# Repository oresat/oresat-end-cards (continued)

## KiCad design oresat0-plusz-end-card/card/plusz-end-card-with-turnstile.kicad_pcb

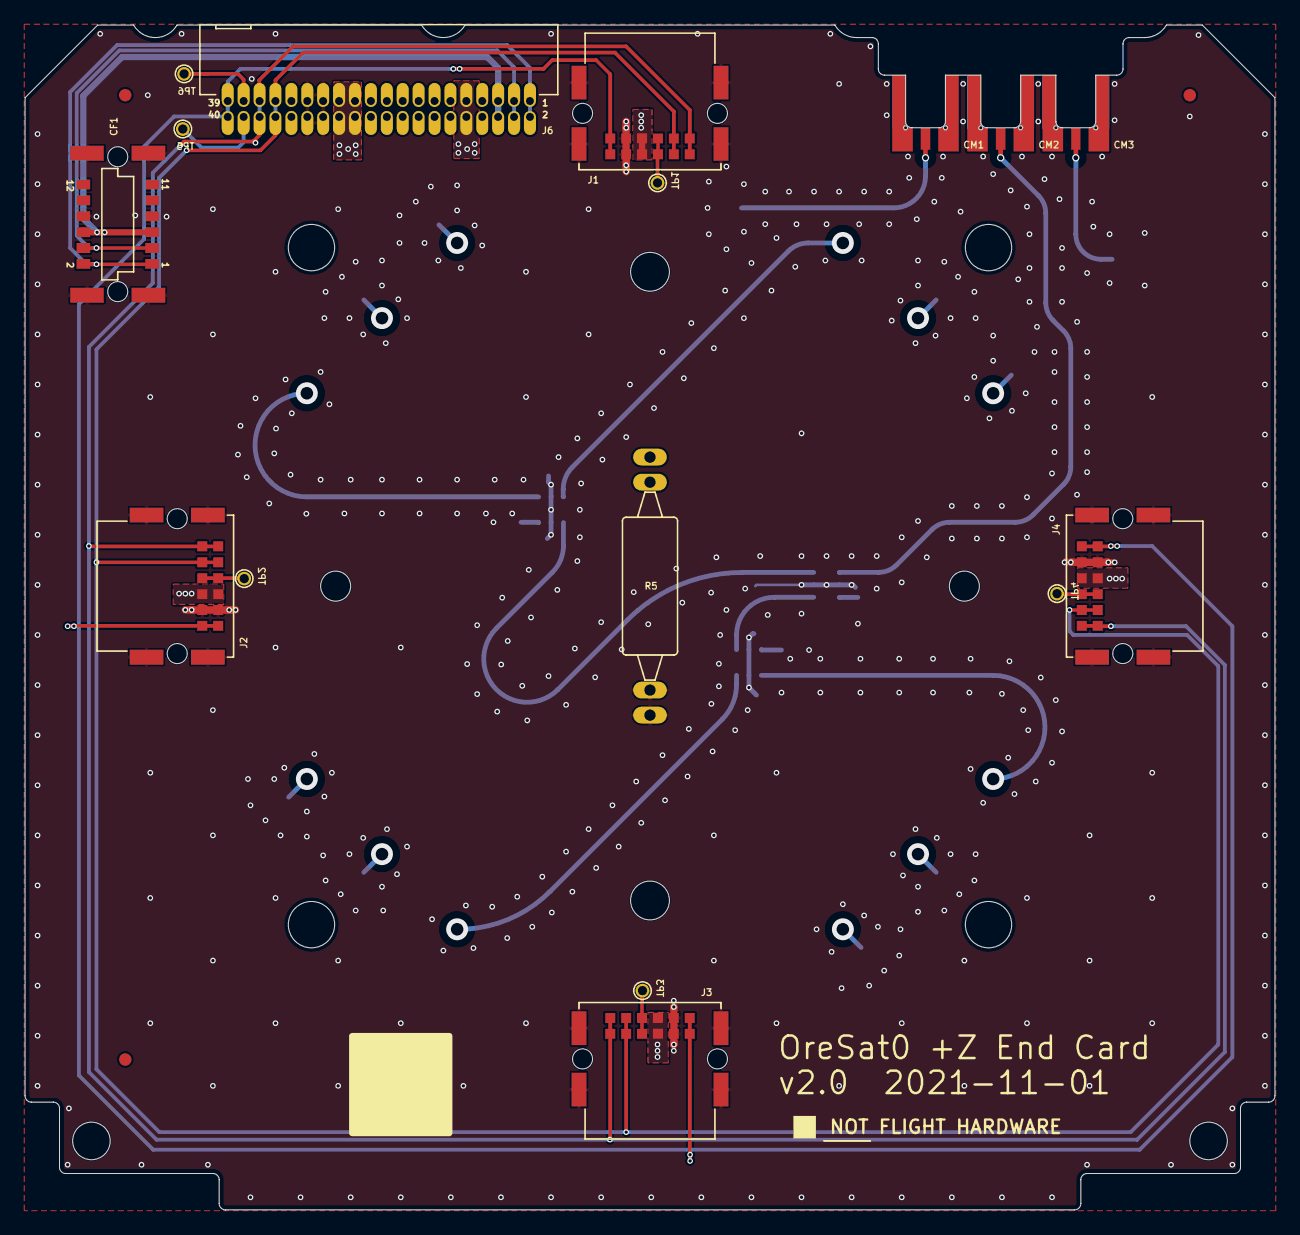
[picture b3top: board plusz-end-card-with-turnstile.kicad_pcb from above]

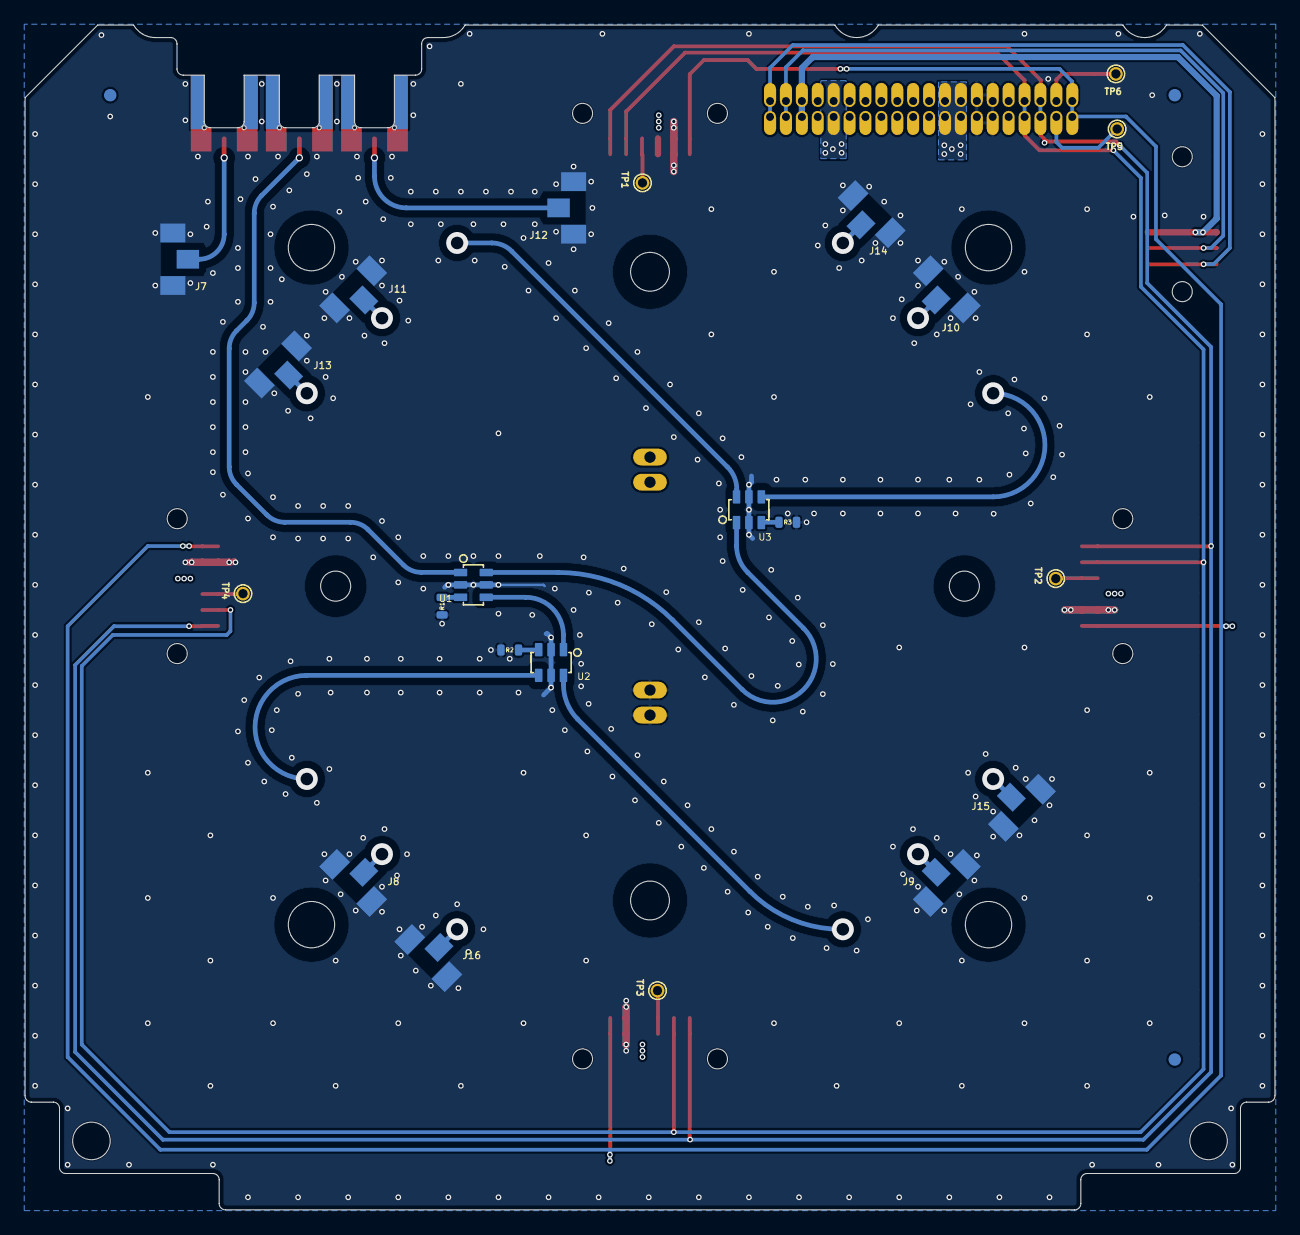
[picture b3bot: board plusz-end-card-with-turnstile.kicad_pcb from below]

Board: 4 copper layers, 99.8 x 94.6 mm, 48 parts (19 on the bottom side), 23 nets.

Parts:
CF1: J-HARWIN-M55-6001242R; HARWIN-M55-60X1242R
CM1, CM2, CM3: J-MOLEX-SMPM-73300-003X; J-MOLEX-SMPM-073300-003X
FIDUCIAL1, FIDUCIAL2, FIDUCIAL3, FIDUCIAL4, FIDUCIAL5, FIDUCIAL6: FIDUCIAL-1.0X2.0
HW1, HW2, HW3, HW4: MCMASTER-94100A150
J1, J2, J3, J4: Harwin M55-7101242R; M55-7101242R
J6: J-SAMTEC-TFM-120-X1-XXX-D-RA
J7, J8, J9, J10, J11, J12, J13, J14, J15, J16: R107064070_CONTACT
PCB1: ORESAT-CARD-V1.3-GENERIC-3RF
R1, R2, R3: 50; .0603-C-NOSILK
R5: 7.5 1W; PAC100-FOR-MELTWIRE
TP1, TP2, TP3, TP4, TP5, TP6: TEST-POINT-LARGE-SQUARE; 1X01
U1, U2, U3: QCN-19+; QCN-XXX+
U$1: FLIGHMARKERNEW; FLIGHTMARKER_NEW_BOARDS
UNK_HOLE_0: dummyfp0
UNK_HOLE_1: dummyfp1
UNK_HOLE_2: dummyfp2
UNK_HOLE_3: dummyfp3

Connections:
/CONNECTORS/C3-UART-RX: J6.38, TP5.1 (1_1)
/CONNECTORS/C3-UART-TX: J6.37, TP6.1 (1_1)
/CONNECTORS/CAN1_H: J1.9 (CANH), J1.10 (CANH), J2.9 (CANH), J2.10 (CANH), J3.9 (CANH), J3.10 (CANH), J4.9 (CANH), J4.10 (CANH), J6.33, J6.34
/CONNECTORS/CAN1_L: J1.11 (CANL), J1.12 (CANL), J2.11 (CANL), J2.12 (CANL), J3.11 (CANL), J3.12 (CANL), J4.11 (CANL), J4.12 (CANL), J6.35, J6.36
/CONNECTORS/MAG-POWER: CF1.5, CF1.6, J6.5, J6.6
/CONNECTORS/MAG-SCL: CF1.3, CF1.4, J6.3, J6.4
/CONNECTORS/MAG-SDA: CF1.1, CF1.2, J6.1, J6.2
/CONNECTORS/TURNSTILE-DEPLOY: J6.9, J6.10, R5.P$3 (2), R5.P$4 (2)
/CONNECTORS/VBUS: J1.5 (VBUS), J1.6 (VBUS), J2.5 (VBUS), J2.6 (VBUS), J3.5 (VBUS), J3.6 (VBUS), J4.5 (VBUS), J4.6 (VBUS), J6.23, J6.24, J6.25, J6.26
/CONNECTORS/~SD: J1.1 (~SD), J1.2 (~SD), J2.1 (~SD), J2.2 (~SD), J3.1 (~SD), J3.2 (~SD), J4.1 (~SD), J4.2 (~SD), J6.39, J6.40
/L1 BAND/RF-L1BAND: CM1.RF (CENTER), J12.P$1
/L BAND/RF-LBAND: CM2.RF (CENTER), U1.1 (SUM)
/L BAND/RF-LBAND-1/4L: U1.6 (PORT2), U3.1 (SUM)
/L BAND/RF-LBAND-SHORT: U1.4 (PORT1), U2.1 (SUM)
/UHF/RF-UHF: CM3.RF (CENTER), J7.P$1
GND: CF1.7, CF1.8, CF1.P$1 (SHIELDS), CF1.P$2 (SHIELDS), CF1.P$3 (SHIELDS), CF1.P$4 (SHIELDS), CM1.P$1 (SHIELD3), CM1.P$2 (SHIELD2), CM1.P$3 (SHIELD1), CM1.P$4 (SHIELD), CM2.P$1 (SHIELD3), CM2.P$2 (SHIELD2), CM2.P$3 (SHIELD1), CM2.P$4 (SHIELD), CM3.P$1 (SHIELD3), CM3.P$2 (SHIELD2), CM3.P$3 (SHIELD1), CM3.P$4 (SHIELD), J1.3 (GND), J1.4 (GND), J1.P$1 (SHIELD), J1.P$2 (SHIELD), J1.P$3 (SHIELD), J1.P$4 (SHIELD), J2.3 (GND), J2.4 (GND), J2.P$1 (SHIELD), J2.P$2 (SHIELD), J2.P$3 (SHIELD), J2.P$4 (SHIELD), J3.3 (GND), J3.4 (GND), J3.P$1 (SHIELD), J3.P$2 (SHIELD), J3.P$3 (SHIELD), J3.P$4 (SHIELD), J4.3 (GND), J4.4 (GND), J4.P$1 (SHIELD), J4.P$2 (SHIELD), J4.P$3 (SHIELD), J4.P$4 (SHIELD), J6.27, J6.28, J6.29, J6.30, J7.P$2, J7.P$3, J8.P$2, J8.P$3, J9.P$2, J9.P$3, J10.P$2, J10.P$3, J11.P$2, J11.P$3, J12.P$2, J12.P$3, J13.P$2, J13.P$3, J14.P$2, J14.P$3, J15.P$2, J15.P$3, J16.P$2, J16.P$3, R1.1, R2.1, R3.1, R5.P$1 (1), R5.P$2 (1), U1.2 (GND), U1.5 (GND), U2.2 (GND), U2.5 (GND), U3.2 (GND), U3.5 (GND)
unnamed: J1.7 (AUX), J1.8 (AUX), TP1.1 (1_1)
unnamed: J2.7 (AUX), J2.8 (AUX), TP2.1 (1_1)
unnamed: J3.7 (AUX), J3.8 (AUX), TP3.1 (1_1)
unnamed: J4.7 (AUX), J4.8 (AUX), TP4.1 (1_1)
unnamed: R1.2, U1.3 (TERM)
unnamed: R2.2, U2.3 (TERM)
unnamed: R3.2, U3.3 (TERM)

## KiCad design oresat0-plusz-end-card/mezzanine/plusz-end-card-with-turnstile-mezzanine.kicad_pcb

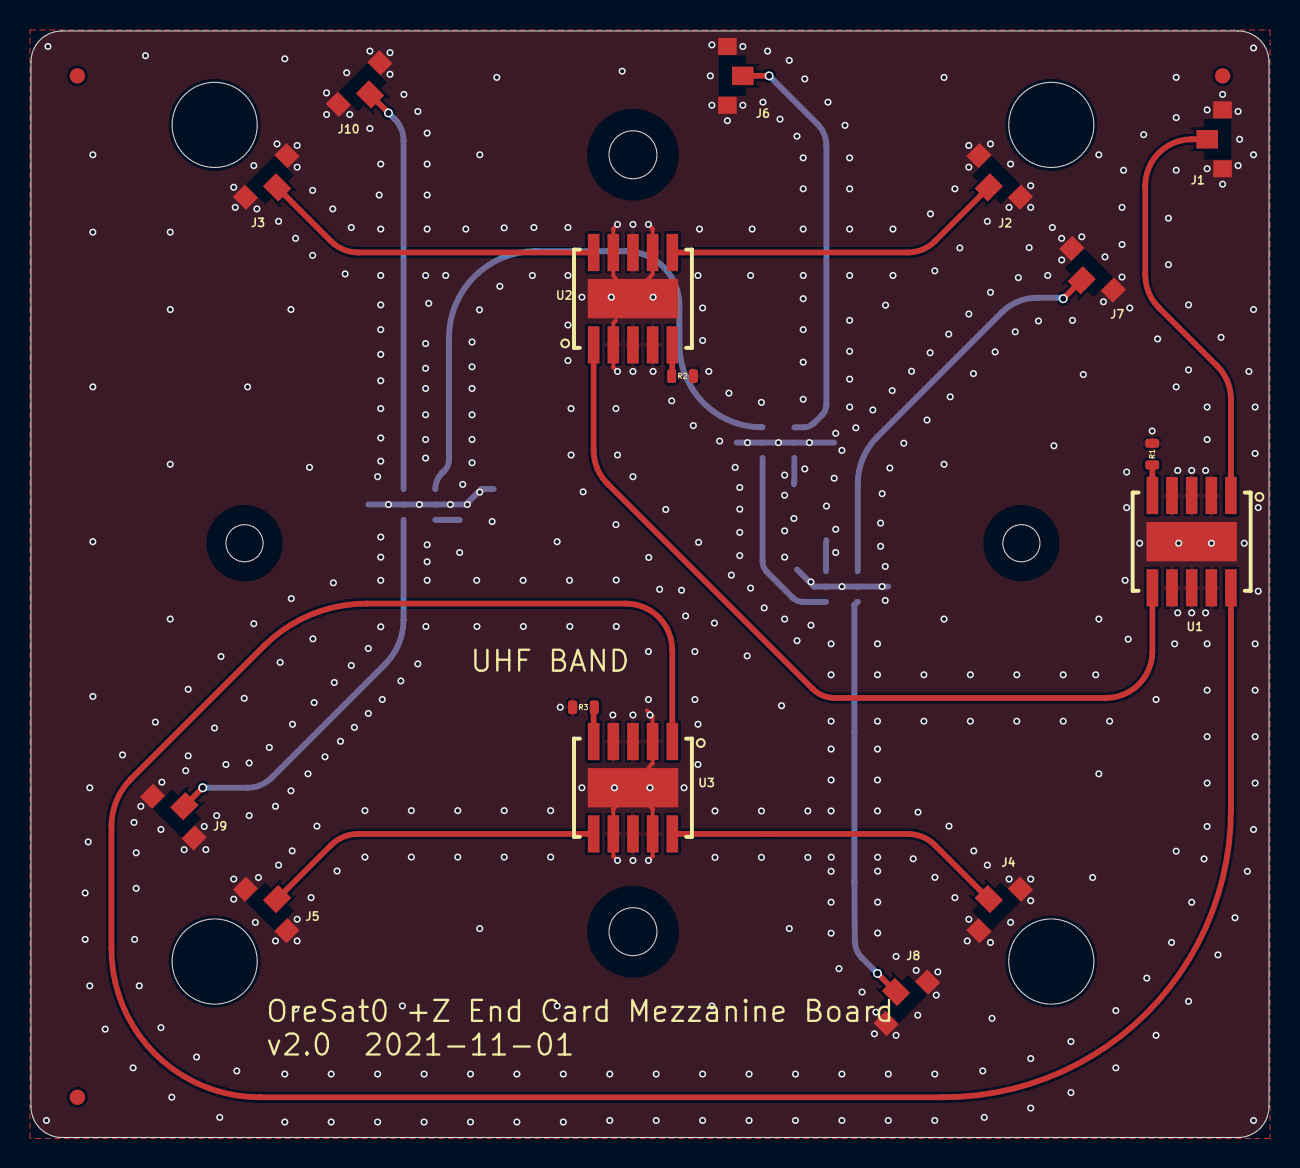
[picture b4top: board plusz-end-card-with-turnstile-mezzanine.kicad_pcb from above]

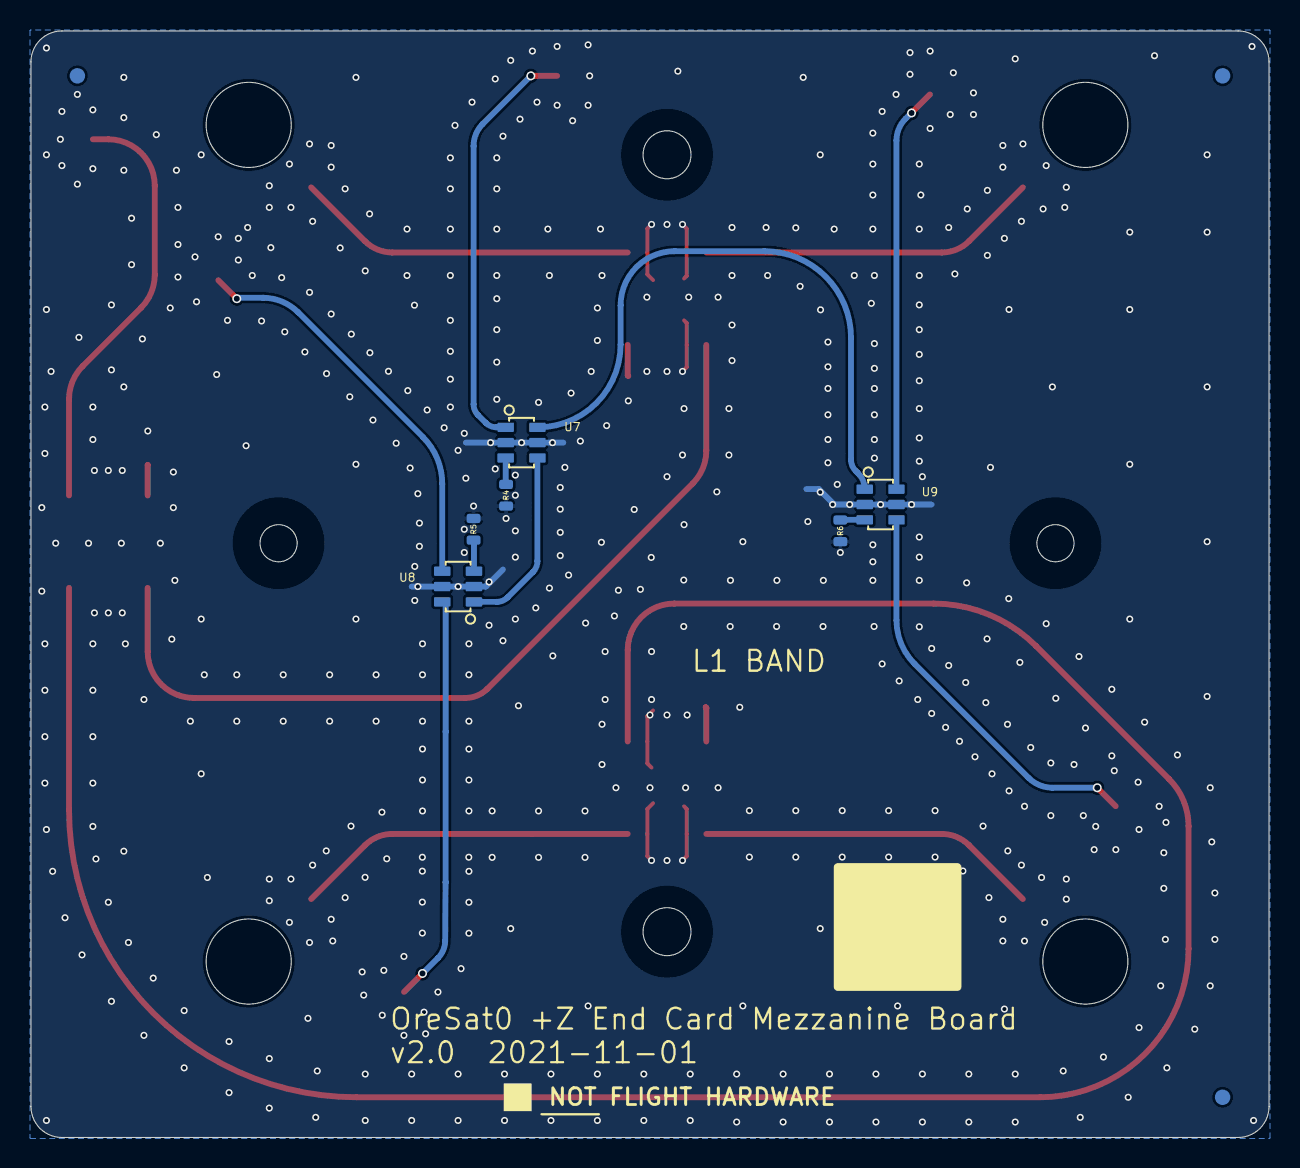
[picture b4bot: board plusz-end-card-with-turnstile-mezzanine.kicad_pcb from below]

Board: 4 copper layers, 80.0 x 71.5 mm, 37 parts (10 on the bottom side), 21 nets.

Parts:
FIDUCIAL1, FIDUCIAL2, FIDUCIAL3, FIDUCIAL4, FIDUCIAL6, FIDUCIAL7: FIDUCIAL-1.0X2.0
J1, J2, J3, J4, J5, J6, J7, J8, J9, J10: R107064070; R107064070_SOLDER
R1, R2, R3, R4, R5, R6: 50; .0603-C-NOSILK
U1, U2, U3: QBA-07+
U7, U8, U9: QCN-19+; QCN-XXX+
U$1: FLIGHMARKERNEW; FLIGHTMARKER_NEW_BOARDS
UNK_HOLE_0: dummyfp0
UNK_HOLE_1: dummyfp1
UNK_HOLE_2: dummyfp2
UNK_HOLE_3: dummyfp3
UNK_HOLE_4: dummyfp4
UNK_HOLE_5: dummyfp5
UNK_HOLE_6: dummyfp6
UNK_HOLE_7: dummyfp7

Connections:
GND: J1.P$2, J1.P$3, J2.P$2, J2.P$3, J3.P$2, J3.P$3, J4.P$2, J4.P$3, J5.P$2, J5.P$3, J6.P$2, J6.P$3, J7.P$2, J7.P$3, J8.P$2, J8.P$3, J9.P$2, J9.P$3, J10.P$2, J10.P$3, R1.1, R2.1, R3.1, R4.1, R5.1, R6.1, U1.2, U1.3, U1.4, U1.7, U1.8, U1.9, U1.GND-NO-PAD, U2.2, U2.3, U2.4, U2.7, U2.8, U2.9, U2.GND-NO-PAD, U3.2, U3.3, U3.4, U3.7, U3.8, U3.9, U3.GND-NO-PAD, U7.2, U7.5, U8.2, U8.5, U9.2, U9.5
L1BAND: J6.P$1, U7.1
L1BAND-SHORT: U7.4, U8.1
L1BAND-SHORT+1/4WAVE: U7.6, U9.1
L1BAND_0: J7.P$1, U8.4
L1BAND_90: J8.P$1, U8.6
L1BAND_180: J9.P$1, U9.4
L1BAND_270: J10.P$1, U9.6
unnamed: R4.2, U7.3
unnamed: R5.2, U8.3
unnamed: R1.2, U1.5
unnamed: R2.2, U2.5
unnamed: R6.2, U9.3
unnamed: R3.2, U3.5
UHF: J1.P$1, U1.1
UHF-SHORT: U1.6, U2.1
UHF-SHORT+1/4WAVE: U1.10, U3.1
UHF_0: J2.P$1, U2.6
UHF_90: J3.P$1, U2.10
UHF_180: J5.P$1, U3.6
UHF_270: J4.P$1, U3.10

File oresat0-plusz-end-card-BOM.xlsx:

Bill Of Materials for OreSat0 +Z End Card and Mezzanine
Last modified: 2021/11/01
PCB version: 2.0 |  |  | P/DNP = | Place/Do Not Place (DNP is for final production boards)
BOM revision: 0 |  |  | Generic = | Any generic part with the same characteristics are OK (e.g., bypass cap)
 | +Z END CARD
Cnt | Part References | P/DNP | Mfg | Mfg PN | Description | Generic | Dist | Dist Part Number | Stock | Cost | Cost Ext.
1 | CF1 | P | Harwin Inc. | M55-6001242R | 12 Position Receptacle Connector 0.050" (1.27mm) Surface Mount Gold | N | Digi-Key | 952-3835-1-ND | 7 | 1.74 | 1.74
3 | CM1, CM2, CM3 | P | Molex | 73300-0020 | SMPM Connector Plug, Male Pin 50Ohm Board Edge | N | Digi-Key | WM10772-ND | 0 | 16.41 | 49.230000000000004
4 | HW1, HW2, HW3, HW4 | P | McMaster Carr | 94100A150 | M2 x 0.4 mm 18-8 Stainless Steel Press-Fit Nut | N | McMaster Carr | 94100A150 | 24 | 0.56200000000000006 | 2.2480000000000002
4 | J1, J2, J3, J4 | P | Harwin Inc. | M55-7101242R | CONN HEADER SMD R/A 12POS 1.27MM -- Solar connectors | N | Digi-Key | 952-3891-1-ND | 30 | 1.46 | 5.8399999999999999
1 | J6 | P | Samtec Inc. | TFM-120-01-L-D-RA | CONN HEADER R/A 40POS 1.27MM - Main OreSat connector | N | Digi-Key | SAM10145-ND | 19 | 10.119999999999999 | 10.119999999999999
3 | R1, R2, R3 | P | Vishay Dale | RCP0603W50R0GEB | RES SMD 50 OHM 2% 1.5W 0603 | N | Digi-Key | 541-2655-1-ND | 20 | 1.8400000000000001 | 5.5200000000000005
1 | R4 | P | Vishay | PAC100007508FA1000 | Res 7.5 ohm 1W 1% Axial high temperature | N | Digi-Key | PPC1D1.0CT-ND | 4 | 0.77000000000000002 | 0.77000000000000002
3 | U1, U2, U3 | P | Mini-Circuits | QCN-19+ | Power Splitter/Combiner, 2 Way-90°, 50Ω, 1100-1925 Mhz, LTCC | N | Mouser | 139-QCN-19 | 7 | 13.949999999999999 | 41.849999999999994
 | MEZZANINE
Cnt | Part References | P/DNP | Mfg | Mfg PN | Description | Generic | Dist | Dist Part Number |  | Cost | Cost Ext.
10 | J1, J2, J3, J4, J5, J6, J7, J8, J9, J10 | P | Radiall | R107064070 | Spring RF connectors | N | Mouser | 501-R107064070 | 29 | 5.1500000000000004 | 51.5
6 | R1, R2, R3, R4, R5, R6 | P | Vishay Dale | RCP0603W50R0GEB | RES SMD 50 OHM 2% 1.5W 0603 | N | Digi-Key | 541-2655-1-ND | 20 | 1.8400000000000001 | 11.040000000000001
3 | U1, U2, U3 | P | Mini-Circuits | QBA-07+ | Power Splitter/Combiner, 2 Way-90°, 50Ω, 340-680 Mhz, LTCC | N | Mini-Circuits | QBA-07+ | 8 | 6.9500000000000002 | 20.850000000000001
3 | U7, U8, U9 | P | Mini-Circuits | QCN-19+ | Power Splitter/Combiner, 2 Way-90°, 50Ω, 1100-1925 Mhz, LTCC | N | Mouser | 139-QCN-19 | 7 | 13.949999999999999 | 41.849999999999994
 |  |  |  |  |  |  |  | Total |  |  | 242.55799999999999

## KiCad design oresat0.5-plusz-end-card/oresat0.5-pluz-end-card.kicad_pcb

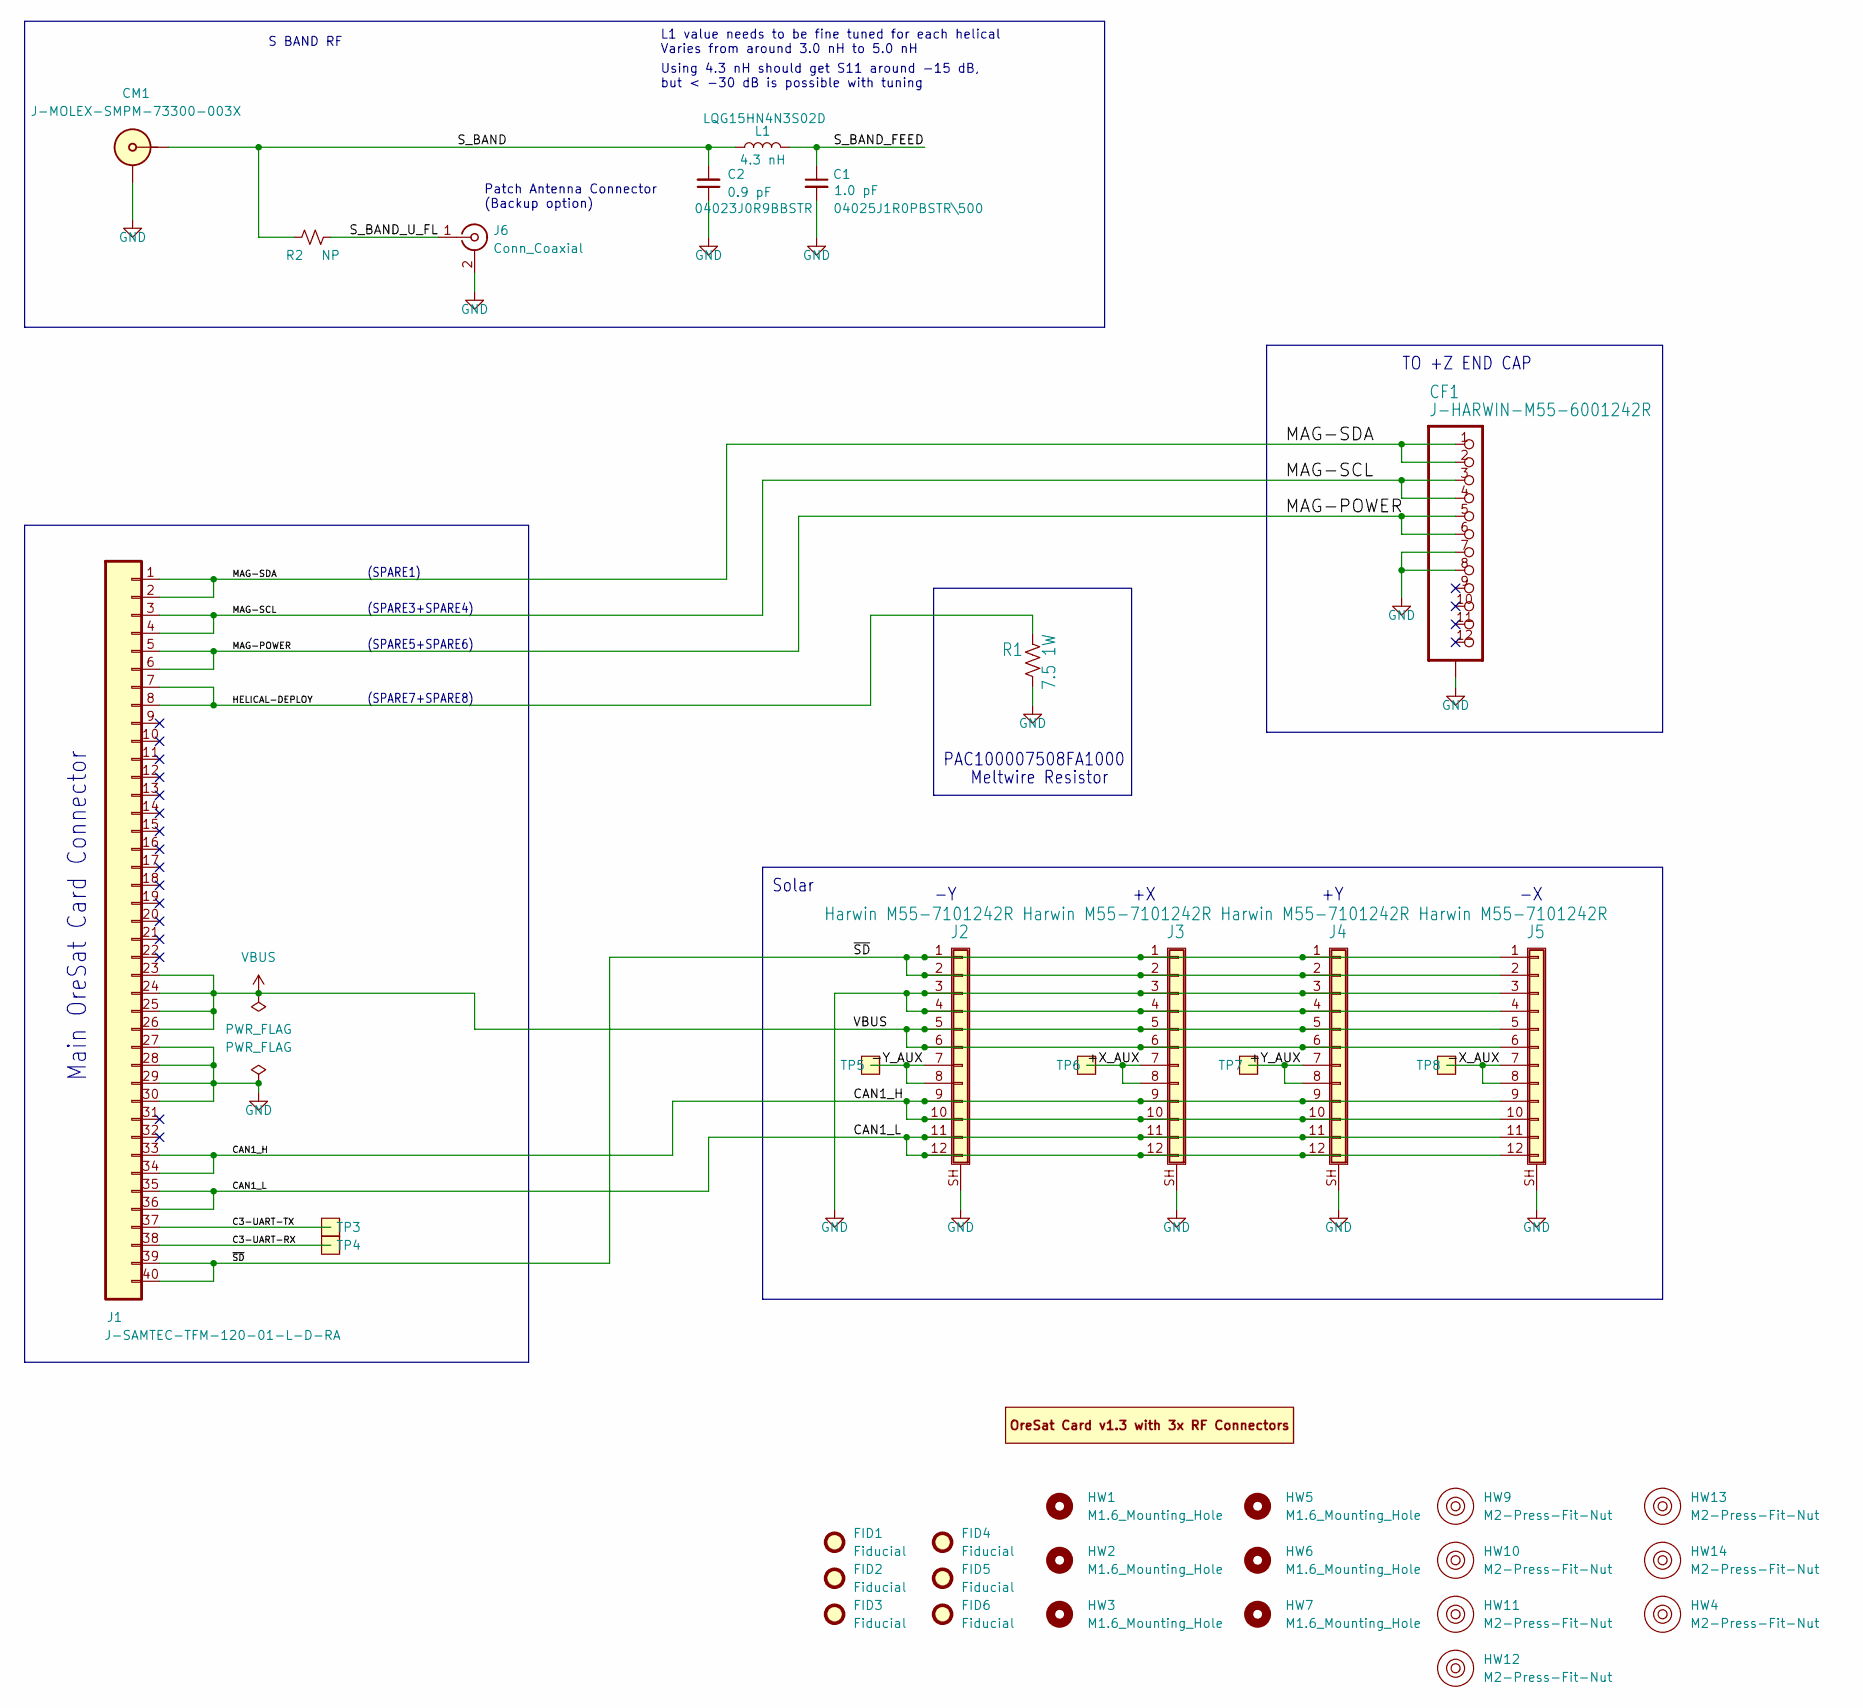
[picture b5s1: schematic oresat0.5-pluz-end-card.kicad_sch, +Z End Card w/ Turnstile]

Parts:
C1: 1.0 pF; C_0402_1005Metric; MPN 04025J1R0PBSTR\500
C2: 0.9 pF; C_0402_1005Metric; MPN 04023J0R9BBSTR
CF1: J-HARWIN-M55-6001242R; J-Harwin-M55-60X1242R; MPN M55-6021242R
CM1: J-MOLEX-SMPM-73300-003X; J-MOLEX-SMPM-073300-002X; MPN 952-3851-1-ND
FID1, FID2, FID3, FID4, FID5, FID6: Fiducial; Fiducial_1mm_Mask2mm
HW1, HW2, HW3, HW5, HW6, HW7: M1.6_Mounting_Hole; M1.6 Mounting Hole
HW4, HW9, HW10, HW11, HW12, HW13, HW14: M2-Press-Fit-Nut
J1: J-SAMTEC-TFM-120-01-L-D-RA; J-SAMTEC-TFM-120-X1-XXX-D-RA; MPN TFM-120-01-L-D-RA
J2, J3, J4, J5: Harwin M55-7101242R; J-Harwin-M55-7101242R; MPN M55-7101242R
J6: Conn_Coaxial; U.FL_Hirose_U.FL-R-SMT-1_Vertical; MPN U.FL-R-SMT-1(10)
L1: 4.3 nH; L_0402_1005Metric; MPN LQG15HN4N3S02D
PCB1: ORESAT-CARD-V1.3-GENERIC-3RF; ORESAT-CARD-V1.3-3RF
R1: 7.5 1W; R-PAC100-FOR-MELTWIRE; MPN PAC100007508FA1000
R2: NP; R_0402_1005Metric; MPN RMCF0603ZT0R00
TP3, TP4, TP5, TP6, TP7, TP8: TestPoint-MinTH; TestPoint-0.75mm-th

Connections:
/+X_AUX: J3.7, J3.8, TP6.1
/+Y_AUX: J4.7, J4.8, TP7.1
/-X_AUX: J5.7, J5.8, TP8.1
/-Y_AUX: J2.7, J2.8, TP5.1
/C3-UART-RX: J1.38, TP4.1
/C3-UART-TX: J1.37, TP3.1
/CAN1_H: J1.33, J1.34, J2.9, J2.10, J3.9, J3.10, J4.9, J4.10, J5.9, J5.10
/CAN1_L: J1.35, J1.36, J2.11, J2.12, J3.11, J3.12, J4.11, J4.12, J5.11, J5.12
/HELICAL-DEPLOY: J1.7, J1.8, R1.2
/MAG-POWER: CF1.5, CF1.6, J1.5, J1.6
/MAG-SCL: CF1.3, CF1.4, J1.3, J1.4
/MAG-SDA: CF1.1, CF1.2, J1.1, J1.2
/S_BAND: C2.2, CM1.SIG, L1.1, R2.1
/S_BAND_FEED: C1.1, L1.2
/S_BAND_U_FL: J6.1 (In), R2.2
/~SD: J1.39, J1.40, J2.1, J2.2, J3.1, J3.2, J4.1, J4.2, J5.1, J5.2
GND: C1.2, C2.1, CF1.7, CF1.8, CF1.SH (SHIELD), CM1.SHLD, J1.27, J1.28, J1.29, J1.30, J2.3, J2.4, J2.SH (Shield), J3.3, J3.4, J3.SH (Shield), J4.3, J4.4, J4.SH (Shield), J5.3, J5.4, J5.SH (Shield), J6.2 (Ext), R1.1
VBUS: J1.23, J1.24, J1.25, J1.26, J2.5, J2.6, J3.5, J3.6, J4.5, J4.6, J5.5, J5.6

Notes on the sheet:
TO +Z END CAP
(SPARE7+SPARE8)
L1 value needs to be fine tuned for each helical Varies from around 3.0 nH to 5.0 nH
Meltwire Resistor
Using 4.3 nH should get S11 around -15 dB, but < -30 dB is possible with tuning
S BAND RF
Solar
PAC100007508FA1000
(SPARE1)
(SPARE3+SPARE4)
Patch Antenna Connector (Backup option)
Main OreSat Card Connector
(SPARE5+SPARE6)

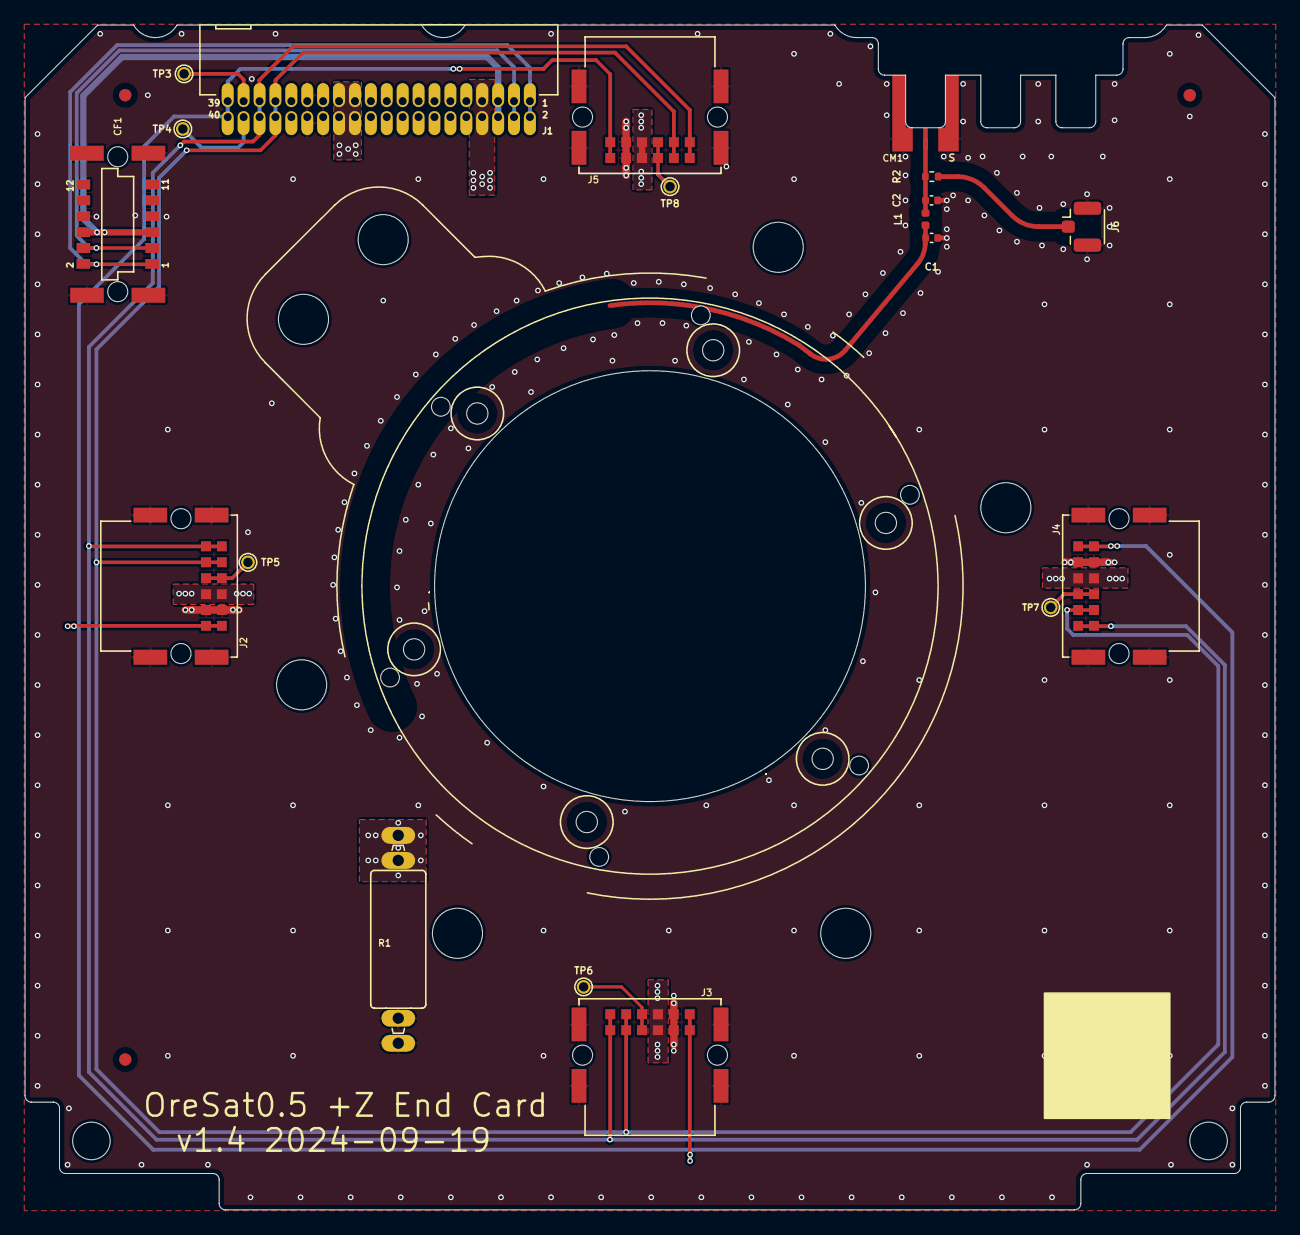
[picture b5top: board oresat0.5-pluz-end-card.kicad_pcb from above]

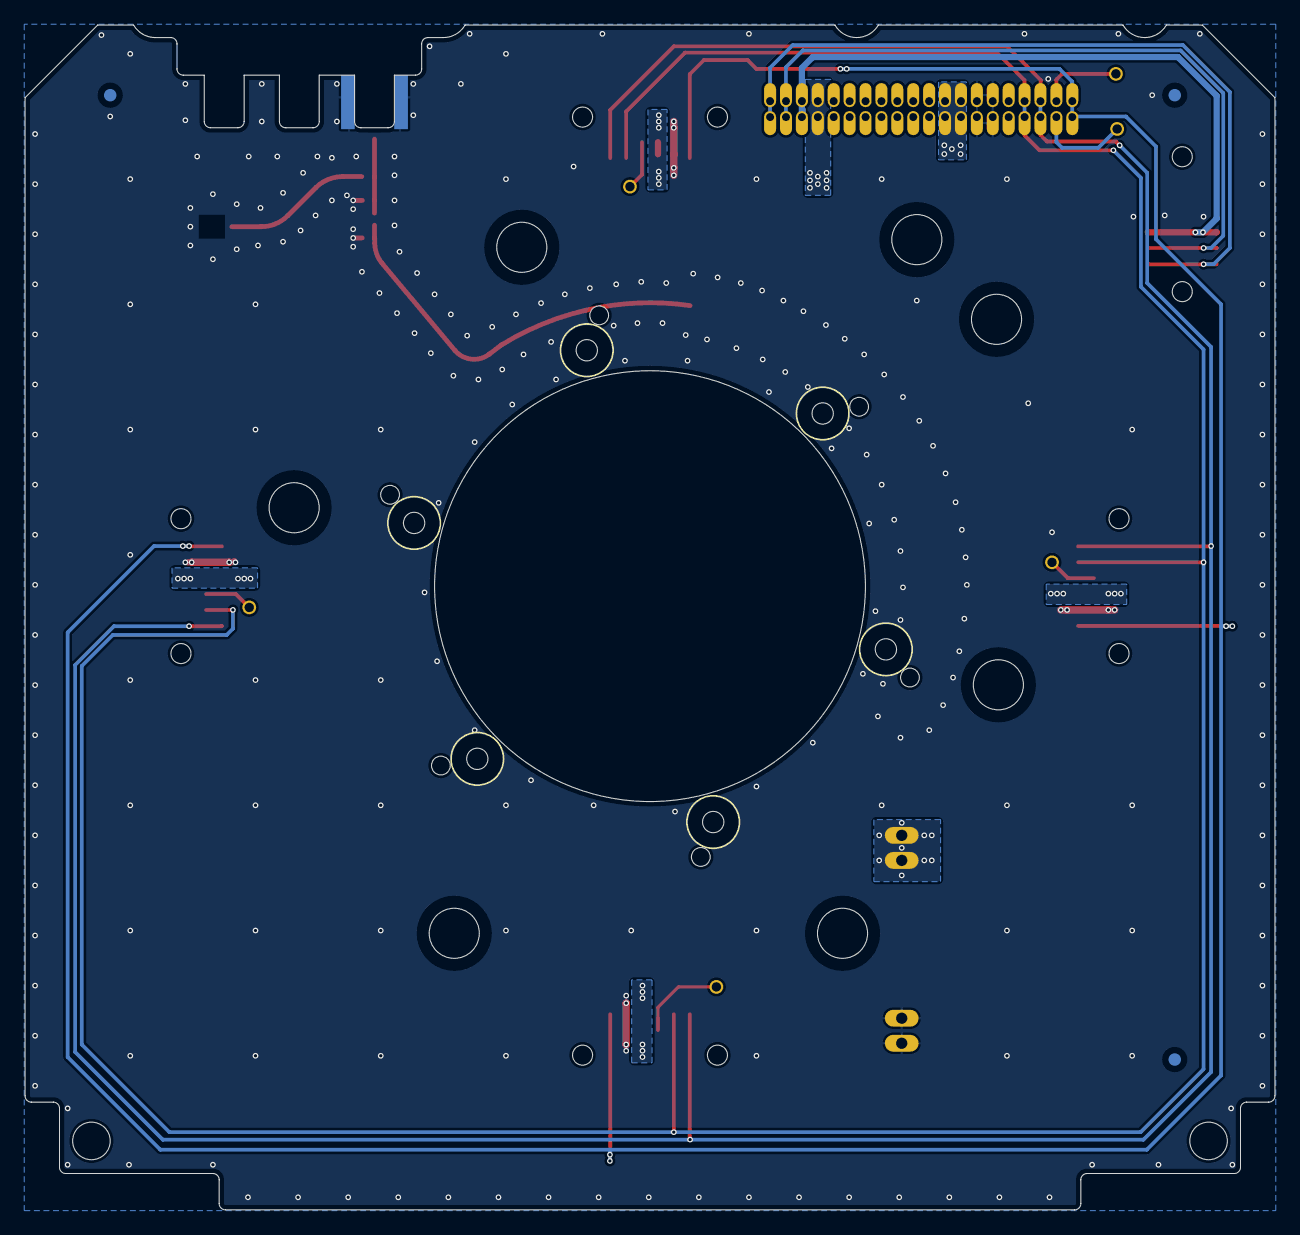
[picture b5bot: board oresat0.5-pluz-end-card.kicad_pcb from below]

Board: 4 copper layers, 99.8 x 94.6 mm, 39 parts (3 on the bottom side), 18 nets.

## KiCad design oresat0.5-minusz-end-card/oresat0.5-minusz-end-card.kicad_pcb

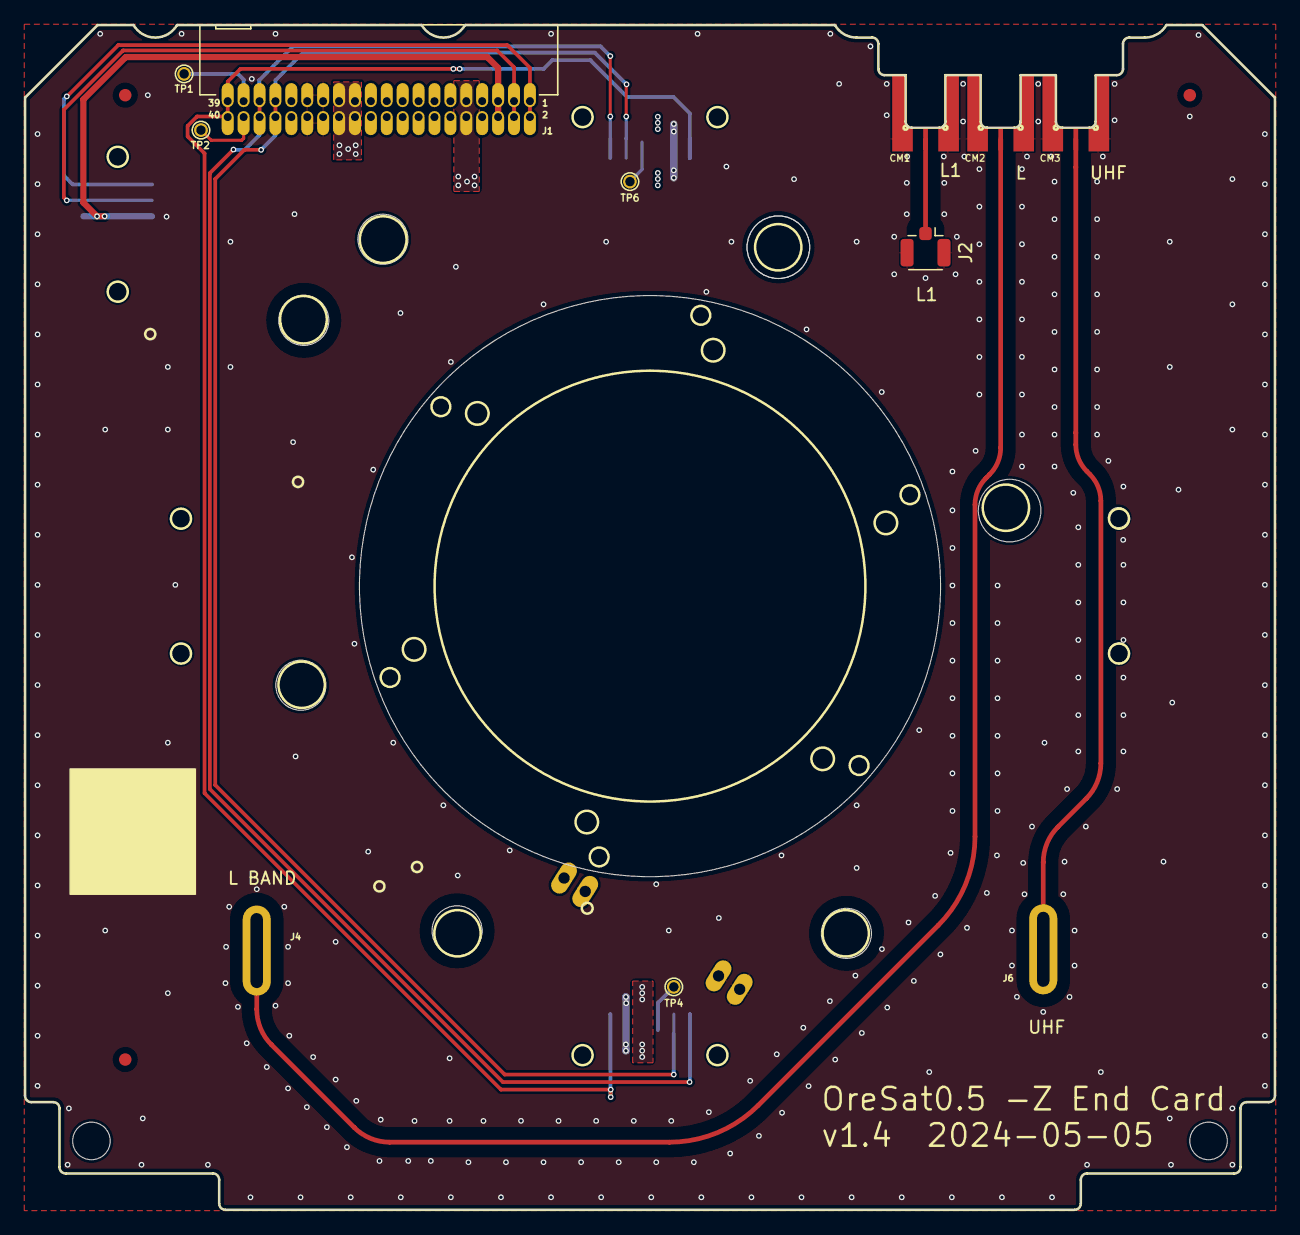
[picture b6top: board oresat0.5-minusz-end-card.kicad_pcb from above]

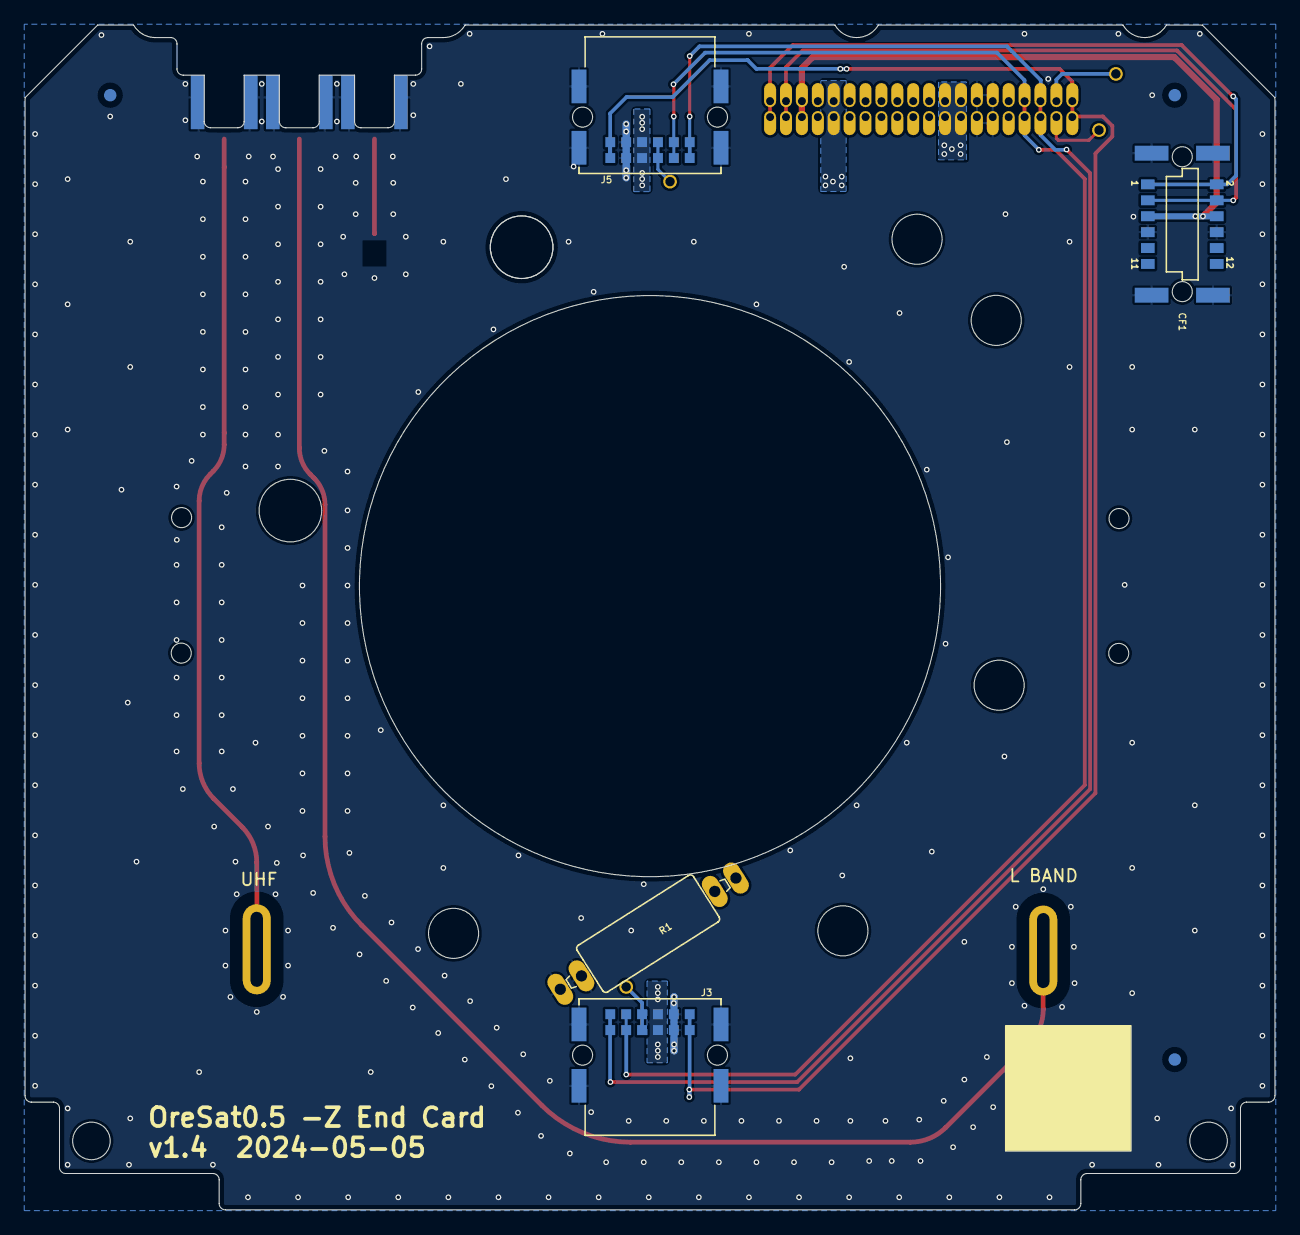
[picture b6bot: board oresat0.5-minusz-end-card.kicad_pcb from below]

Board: 4 copper layers, 99.8 x 94.6 mm, 27 parts (10 on the bottom side), 16 nets.

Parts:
CF1: J-HARWIN-M55-6001242R; J-Harwin-M55-60X1242R
CM1, CM2, CM3: J-MOLEX-SMPM-73300-003X; J-MOLEX-SMPM-073300-002X
FID1, FID2, FID3, FID4, FID5, FID6: Fiducial; Fiducial_1mm_Mask2mm
H107, H108: MountingHole; MountingHole_5mm
HW2, HW3, HW6: M2-Press-Fit-Nut
J1: J-SAMTEC-TFM-120-01-L-D-RA; J-SAMTEC-TFM-120-X1-XXX-D-RA
J2: U.FL-R-SMT-1; U.FL_Hirose_U.FL-R-SMT-1_Vertical
J3, J5: Harwin M55-7101242R; J-Harwin-M55-7101242R
J4, J6: tape-measure-slot-antenna
PCB1: ORESAT-CARD-V1.3-GENERIC-3RF; ORESAT-CARD-V1.3-3RF
R1: 7.5 1W; R-PAC100-FOR-MELTWIRE
TP1, TP2, TP4, TP6: TEST-POINT-LARGE-SQUARE; TestPoint-0.75mm-th

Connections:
/+X_AUX: J5.7, J5.8, TP6.1
/-X_AUX: J3.7, J3.8, TP4.1
/C3-UART-RX: J1.38, TP2.1
/C3-UART-TX: J1.37, TP1.1
/CAN1_H: J1.33, J1.34, J3.9, J3.10, J5.9, J5.10
/CAN1_L: J1.35, J1.36, J3.11, J3.12, J5.11, J5.12
/L1BAND: CM1.SIG, J2.1 (In)
/LBAND: CM2.SIG, J4.1
/MAG-POWER: CF1.5, CF1.6, J1.5, J1.6
/MAG-SCL: CF1.3, CF1.4, J1.3, J1.4
/MAG-SDA: CF1.1, CF1.2, J1.1, J1.2
/TURNSTILE-DEPLOY: J1.9, J1.10, R1.1
/UHF: CM3.SIG, J6.1
/~SD: J1.39, J1.40, J3.1, J3.2, J5.1, J5.2
GND: CF1.7, CF1.8, CF1.SH (SHIELD), CM1.SHLD, CM2.SHLD, CM3.SHLD, J1.27, J1.28, J1.29, J1.30, J2.2 (Ext), J3.3, J3.4, J3.SH (Shield), J5.3, J5.4, J5.SH (Shield), R1.2
VBUS: J1.23, J1.24, J1.25, J1.26, J3.5, J3.6, J5.5, J5.6
